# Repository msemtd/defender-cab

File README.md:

# defender-cab

Another MAME cabinet with the emphasis on Defender.

Started out with the control panel dimensions from the Facebook group. direct conversion to metric followed by a trim of the panel from 24.5 x 8 inches to 600mm x 200mm.

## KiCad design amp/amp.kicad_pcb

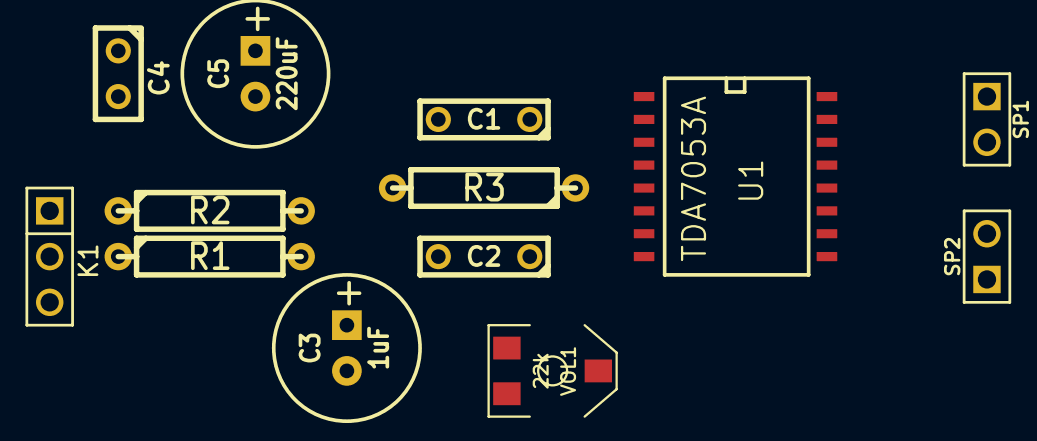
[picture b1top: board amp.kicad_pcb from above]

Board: 2 copper layers, 13 parts (0 on the bottom side), 12 nets, no tracks yet.

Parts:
C1, C2: 470nF; C2
C3: 1uF; C1V8
C4: 100nF; C1
C5: 220uF; C1V8
K1: STEREO; PIN_ARRAY_3X1
R1, R2: 5k; R4
R3: 5k6; R4
SP1, SP2: SPEAKER; PIN_ARRAY_2X1
U1: TDA7053A; SO16W
VOL1: 22k; POT_CMS

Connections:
GNDPWR: C3.2, C4.2, C5.2, K1.3, R1.2, R2.2, U1.7, U1.10, U1.14, VOL1.3
unnamed: SP1.2, U1.13
unnamed: SP2.2, U1.12
unnamed: SP1.1, U1.16
unnamed: SP2.1, U1.9
unnamed: U1.2, U1.8, VOL1.2
unnamed: C1.2, K1.1, R2.1
unnamed: C2.1, U1.6
unnamed: C1.1, U1.4
unnamed: C3.1, R3.2, VOL1.1
unnamed: C2.2, K1.2, R1.1
VCC: C4.1, C5.1, R3.1, U1.5

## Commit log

2015-01-24 first add of various
2015-01-24 back from laser
2015-01-24 now using github for proper distribution
2015-01-24 actual reverse button position on the 3mm ply laser cut
2015-01-27 manuals added
2015-02-07 Jakobud cab plans
2015-02-08 more plans - work at home
2015-02-08 smoothing and rounding
2015-02-17 added theory manual
2015-02-23 KiCAD design for amplifier
2015-02-23 schematic update
2015-03-04 moving components about
2015-03-05 Update of amp circuit and scan of speakers
2015-03-05 added back panel with living hinge
2015-03-09 updates - slight
2015-03-09 cutting plan for 600x400 2mm perspex
